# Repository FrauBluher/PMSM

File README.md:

PMSM
====

Permanent Magnet Syncronous Motor Driver and Supporting Code/Sims

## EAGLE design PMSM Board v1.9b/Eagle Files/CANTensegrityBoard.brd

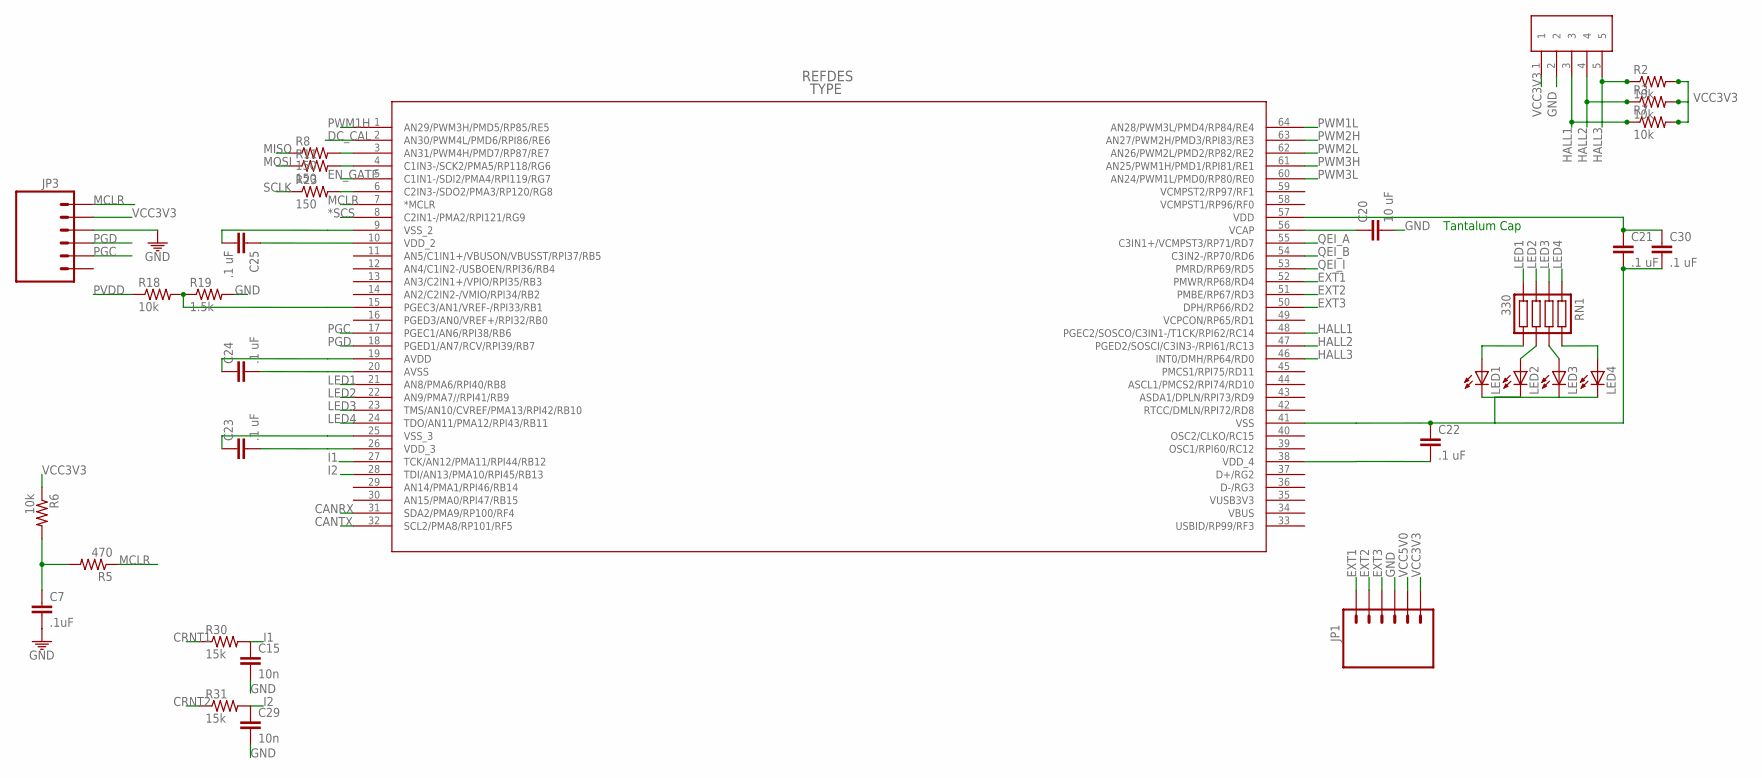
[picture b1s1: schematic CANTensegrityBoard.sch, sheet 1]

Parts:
C7: .1uF; 0805
C15, C29: 10n; 0805
C20: 10 uF; 0805
C21, C22, C23, C24, C25, C30: .1 uF; 0805
JP1: M06DUAL_ROW; 2X03
JP3: M06LOCK; 1X06_LOCK
LED1, LED2, LED3, LED4: LED0805; LED-0805
R2, R3, R6, R7, R18: 10k; 0805
R5: 470; 0805
R8, R11, R23: 150; 0805
R19: 1.5k; 0805
R30, R31: 15k; 0805
RN1: 330; EXB-38V271JV
U6: DSPIC33EP256MU80; QFP64-10X10MC
U$20: MICROCLASP5; 55932-0510

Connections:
*SCS: U6.8 (C2IN1-/PMA2/RPI121/RG9); also elsewhere on the board
CANRX: U6.31 (SDA2/PMA9/RP100/RF4); also elsewhere on the board
CANTX: U6.32 (SCL2/PMA8/RP101/RF5); also elsewhere on the board
CRNT1: R30.1; also elsewhere on the board
CRNT2: R31.1; also elsewhere on the board
DC_CAL: U6.2 (AN30/PWM4L/PMD6/RPI86/RE6); also elsewhere on the board
EN_GATE: U6.5 (C1IN1-/SDI2/PMA4/RPI119/RG7); also elsewhere on the board
EXT1: JP1.1, U6.52 (PMWR/RP68/RD4)
EXT2: JP1.2, U6.51 (PMBE/RP67/RD3)
EXT3: JP1.3, U6.50 (DPH/RP66/RD2)
GND: C7.2, C15.2, C20.2, C21.2, C22.1, C23.1, C24.2, C25.2, C29.2, C30.2, JP1.4, JP3.3, LED1.2 (C), LED2.2 (C), LED3.2 (C), LED4.2 (C), R19.2, U6.9 (VSS_2), U6.20 (AVSS), U6.25 (VSS_3), U6.41 (VSS), U$20.2; also elsewhere on the board
HALL1: R7.1, U6.48 (PGEC2/SOSCO/C3IN1-/T1CK/RPI62/RC14), U$20.3
HALL2: R3.1, U6.47 (PGED2/SOSCI/C3IN3-/RPI61/RC13), U$20.4
HALL3: R2.1, U6.46 (INT0/DMH/RP64/RD0), U$20.5
I1: C15.1, R30.2, U6.27 (TCK/AN12/PMA11/RPI44/RB12)
I2: C29.1, R31.2, U6.28 (TDI/AN13/PMA10/RPI45/RB13)
LED1: RN1.P$4 (4), U6.21 (AN8/PMA6/RPI40/RB8)
LED2: RN1.P$3 (3), U6.22 (AN9/PMA7//RPI41/RB9)
LED3: RN1.P$2 (2), U6.23 (TMS/AN10/CVREF/PMA13/RPI42/RB10)
LED4: RN1.P$1 (1), U6.24 (TDO/AN11/PMA12/RPI43/RB11)
MCLR: JP3.1, R5.1, U6.7 (*MCLR)
MISO: R8.1; also elsewhere on the board
MOSI: R11.1; also elsewhere on the board
unnamed: C7.1, R5.2, R6.2
unnamed: R8.2, U6.3 (AN31/PWM4H/PMD7/RP87/RE7)
unnamed: R11.2, U6.4 (C1IN3-/SCK2/PMA5/RP118/RG6)
unnamed: R23.2, U6.6 (C2IN3-/SDO2/PMA3/RP120/RG8)
unnamed: R18.2, R19.1, U6.15 (PGEC3/AN1/VREF-/RPI33/RB1)
unnamed: C20.1, U6.56 (VCAP)
unnamed: LED1.1 (A), RN1.P$5 (5)
unnamed: LED2.1 (A), RN1.P$6 (6)
unnamed: LED3.1 (A), RN1.P$7 (7)
unnamed: LED4.1 (A), RN1.P$8 (8)
PGC: JP3.5, U6.17 (PGEC1/AN6/RPI38/RB6)
PGD: JP3.4, U6.18 (PGED1/AN7/RCV/RPI39/RB7)
PVDD: R18.1; also elsewhere on the board
PWM1H: U6.1 (AN29/PWM3H/PMD5/RP85/RE5); also elsewhere on the board
PWM1L: U6.64 (AN28/PWM3L/PMD4/RP84/RE4); also elsewhere on the board
PWM2H: U6.63 (AN27/PWM2H/PMD3/RPI83/RE3); also elsewhere on the board
PWM2L: U6.62 (AN26/PWM2L/PMD2/RP82/RE2); also elsewhere on the board
PWM3H: U6.61 (AN25/PWM1H/PMD1/RPI81/RE1); also elsewhere on the board
PWM3L: U6.60 (AN24/PWM1L/PMD0/RP80/RE0); also elsewhere on the board
QEI_A: U6.55 (C3IN1+/VCMPST3/RP71/RD7); also elsewhere on the board
QEI_B: U6.54 (C3IN2-/RP70/RD6); also elsewhere on the board
QEI_I: U6.53 (PMRD/RP69/RD5); also elsewhere on the board
SCLK: R23.1; also elsewhere on the board
VCC3V3: C21.1, C22.2, C23.2, C24.1, C25.1, C30.1, JP1.6, JP3.2, R2.2, R3.2, R6.1, R7.2, U6.10 (VDD_2), U6.19 (AVDD), U6.26 (VDD_3), U6.38 (VDD_4), U6.57 (VDD), U$20.1; also elsewhere on the board
VCC5V0: JP1.5; also elsewhere on the board

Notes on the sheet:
Tantalum Cap

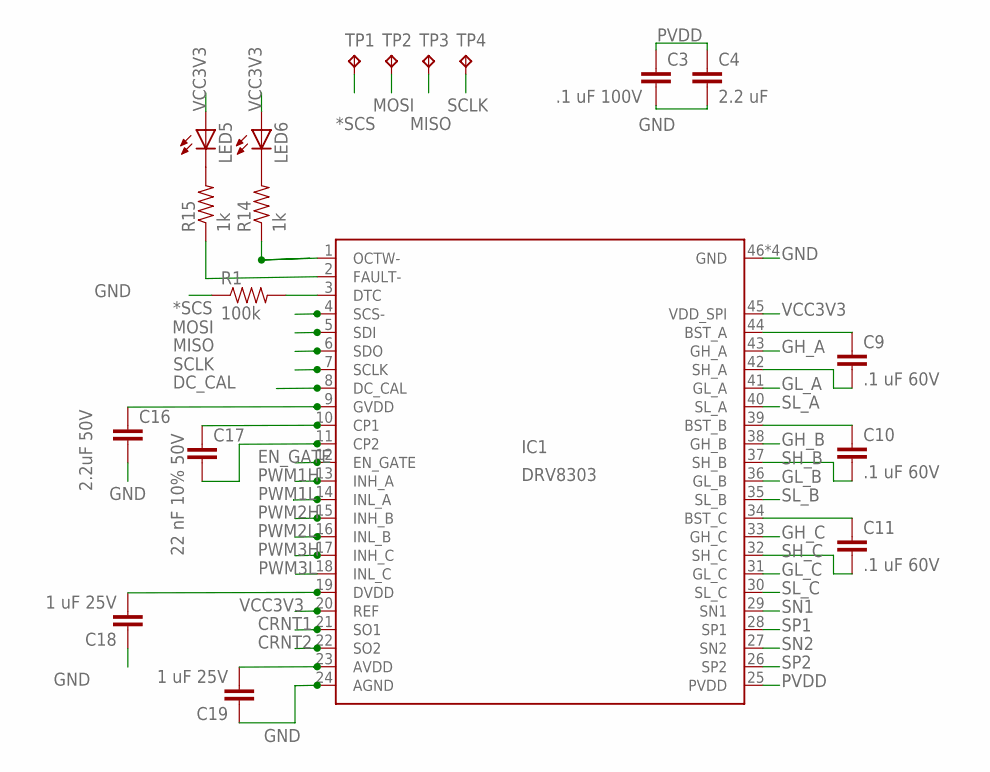
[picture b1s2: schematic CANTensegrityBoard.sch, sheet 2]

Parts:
C3: .1 uF 100V; 0805
C4: 2.2 uF; 0805
C9, C10, C11: .1 uF 60V; 0805
C16: 2.2uF 50V; 0805
C17: 22 nF 10% 50V; 0805
C18, C19: 1 uF 25V; 0805
IC1: DRV8303; HTSSOP-480-DCA
LED5, LED6: LED0805; LED-0805
R1: 100k; 0805
R14, R15: 1k; 0805
TP1, TP2, TP3, TP4: TPTP06R; TP06R

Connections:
*SCS: IC1.4 (SCS-), TP1.TP; also elsewhere on the board
BST_B: C10.1, IC1.39 (BST_B)
BST_C: C11.1, IC1.34 (BST_C)
CRNT1: IC1.21 (SO1); also elsewhere on the board
CRNT2: IC1.22 (SO2); also elsewhere on the board
DC_CAL: IC1.8 (DC_CAL); also elsewhere on the board
EN_GATE: IC1.12 (EN_GATE); also elsewhere on the board
GH_A: IC1.43 (GH_A); also elsewhere on the board
GH_B: IC1.38 (GH_B); also elsewhere on the board
GH_C: IC1.33 (GH_C); also elsewhere on the board
GL_A: IC1.41 (GL_A); also elsewhere on the board
GL_B: IC1.36 (GL_B); also elsewhere on the board
GL_C: IC1.31 (GL_C); also elsewhere on the board
GND: C3.2, C4.2, C16.2, C18.1, C19.1, IC1.24 (AGND), IC1.46 (GND), IC1.47 (GND), IC1.48 (GND), IC1.49 (GND), R1.1; also elsewhere on the board
MISO: IC1.6 (SDO), TP3.TP; also elsewhere on the board
MOSI: IC1.5 (SDI), TP2.TP; also elsewhere on the board
unnamed: IC1.3 (DTC), R1.2
unnamed: C9.1, IC1.44 (BST_A)
unnamed: LED5.2 (C), R15.2
unnamed: IC1.1 (OCTW-), R14.1
unnamed: LED6.2 (C), R14.2
unnamed: C16.1, IC1.9 (GVDD)
unnamed: C17.1, IC1.10 (CP1)
unnamed: C17.2, IC1.11 (CP2)
unnamed: C18.2, IC1.19 (DVDD)
unnamed: C19.2, IC1.23 (AVDD)
unnamed: IC1.2 (FAULT-), R15.1
PVDD: C3.1, C4.1, IC1.25 (PVDD); also elsewhere on the board
PWM1H: IC1.13 (INH_A); also elsewhere on the board
PWM1L: IC1.14 (INL_A); also elsewhere on the board
PWM2H: IC1.15 (INH_B); also elsewhere on the board
PWM2L: IC1.16 (INL_B); also elsewhere on the board
PWM3H: IC1.17 (INH_C); also elsewhere on the board
PWM3L: IC1.18 (INL_C); also elsewhere on the board
SCLK: IC1.7 (SCLK), TP4.TP; also elsewhere on the board
SH_A: C9.2, IC1.42 (SH_A); also elsewhere on the board
SH_B: C10.2, IC1.37 (SH_B); also elsewhere on the board
SH_C: C11.2, IC1.32 (SH_C); also elsewhere on the board
SL_A: IC1.40 (SL_A); also elsewhere on the board
SL_B: IC1.35 (SL_B); also elsewhere on the board
SL_C: IC1.30 (SL_C); also elsewhere on the board
SN1: IC1.29 (SN1); also elsewhere on the board
SN2: IC1.27 (SN2); also elsewhere on the board
SP1: IC1.28 (SP1); also elsewhere on the board
SP2: IC1.26 (SP2); also elsewhere on the board
VCC3V3: IC1.20 (REF), IC1.45 (VDD_SPI), LED5.1 (A), LED6.1 (A); also elsewhere on the board

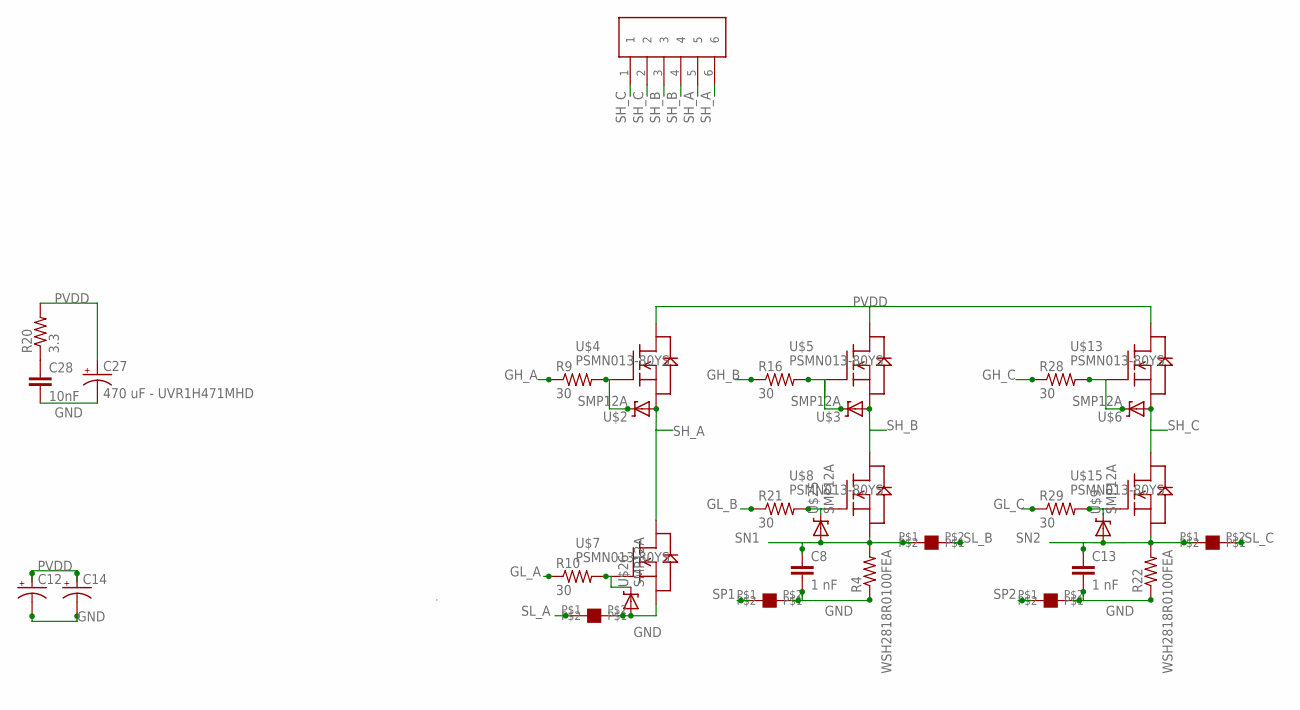
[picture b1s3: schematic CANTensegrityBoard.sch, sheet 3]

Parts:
C8, C13: 1 nF; 0805
C12, C14: CAP_POLPTH2; CPOL-RADIAL-10UF-25V
C27: 470 uF - UVR1H471MHD; CPOL-RADIAL-1000UF-25V
C28: 10nF; 0805
R4, R22: WSH2818R0100FEA; SMT-REF
R9, R10, R16, R21, R28, R29: 30; 0805
R20: 3.3; 0805
U$2, U$3, U$6, U$9, U$25, U$26: SMP12A; DO-220AA
U$4, U$5, U$7, U$8, U$13, U$15: PSMN013-80YS; TO127P600X120-5N
U$10, U$11, U$12, U$23, U$24: NETJUMPER
U$17: MINIFITJR6PIN; 0039288060

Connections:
GH_A: R9.1; also elsewhere on the board
GH_B: R16.1; also elsewhere on the board
GH_C: R28.1; also elsewhere on the board
GL_A: R10.1; also elsewhere on the board
GL_B: R21.1; also elsewhere on the board
GL_C: R29.1; also elsewhere on the board
GND: C8.2, C12.2 (-), C13.2, C14.2 (-), C27.2 (-), C28.2, R4.1, R22.1, U$7.1 (S), U$7.2 (S), U$7.3 (S), U$10.P$2, U$11.P$2, U$23.P$2, U$26.ANODE (A); also elsewhere on the board
unnamed: C28.1, R20.1
unnamed: R9.2, U$2.CATHODE (C), U$4.4 (G)
unnamed: R10.2, U$7.4 (G), U$26.CATHODE (C)
unnamed: R16.2, U$3.CATHODE (C), U$5.4 (G)
unnamed: R21.2, U$8.4 (G), U$25.CATHODE (C)
unnamed: R28.2, U$6.CATHODE (C), U$13.4 (G)
unnamed: R29.2, U$9.CATHODE (C), U$15.4 (G)
PVDD: C12.1 (+), C14.1 (+), C27.1 (+), R20.2, U$4.5 (D), U$4.P$1 (D), U$4.P$2 (D), U$4.P$3 (D), U$4.P$4 (D), U$4.P$5 (D), U$4.P$6 (D), U$4.P$7 (D), U$4.P$8 (D), U$4.P$9 (D), U$5.5 (D), U$5.P$1 (D), U$5.P$2 (D), U$5.P$3 (D), U$5.P$4 (D), U$5.P$5 (D), U$5.P$6 (D), U$5.P$7 (D), U$5.P$8 (D), U$5.P$9 (D), U$13.5 (D), U$13.P$1 (D), U$13.P$2 (D), U$13.P$3 (D), U$13.P$4 (D), U$13.P$5 (D), U$13.P$6 (D), U$13.P$7 (D), U$13.P$8 (D), U$13.P$9 (D); also elsewhere on the board
SH_A: U$2.ANODE (A), U$4.1 (S), U$4.2 (S), U$4.3 (S), U$7.5 (D), U$7.P$1 (D), U$7.P$2 (D), U$7.P$3 (D), U$7.P$4 (D), U$7.P$5 (D), U$7.P$6 (D), U$7.P$7 (D), U$7.P$8 (D), U$7.P$9 (D), U$17.5, U$17.6; also elsewhere on the board
SH_B: U$3.ANODE (A), U$5.1 (S), U$5.2 (S), U$5.3 (S), U$8.5 (D), U$8.P$1 (D), U$8.P$2 (D), U$8.P$3 (D), U$8.P$4 (D), U$8.P$5 (D), U$8.P$6 (D), U$8.P$7 (D), U$8.P$8 (D), U$8.P$9 (D), U$17.3, U$17.4; also elsewhere on the board
SH_C: U$6.ANODE (A), U$13.1 (S), U$13.2 (S), U$13.3 (S), U$15.5 (D), U$15.P$1 (D), U$15.P$2 (D), U$15.P$3 (D), U$15.P$4 (D), U$15.P$5 (D), U$15.P$6 (D), U$15.P$7 (D), U$15.P$8 (D), U$15.P$9 (D), U$17.1, U$17.2; also elsewhere on the board
SL_A: U$10.P$1; also elsewhere on the board
SL_B: U$12.P$2; also elsewhere on the board
SL_C: U$24.P$2; also elsewhere on the board
SN1: C8.1, R4.2, U$8.1 (S), U$8.2 (S), U$8.3 (S), U$12.P$1, U$25.ANODE (A); also elsewhere on the board
SN2: C13.1, R22.2, U$9.ANODE (A), U$15.1 (S), U$15.2 (S), U$15.3 (S), U$24.P$1; also elsewhere on the board
SP1: U$11.P$1; also elsewhere on the board
SP2: U$23.P$1; also elsewhere on the board

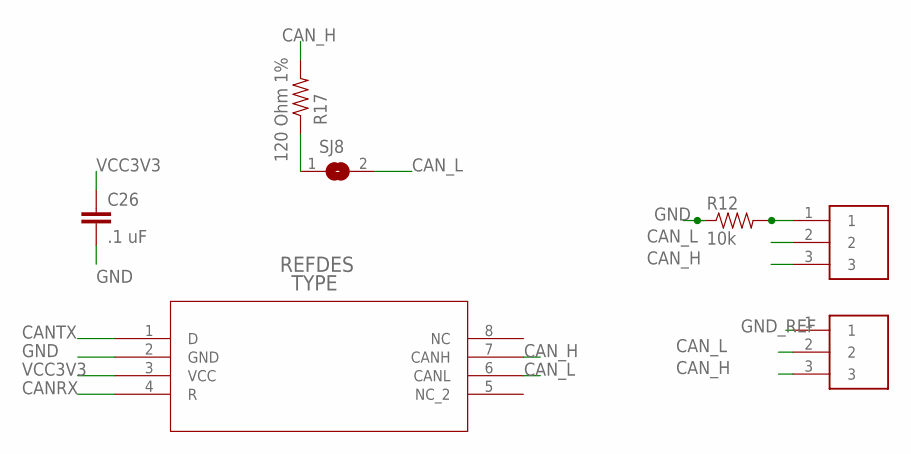
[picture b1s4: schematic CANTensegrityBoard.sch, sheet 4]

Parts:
C26: .1 uF; 0805
R12: 10k; 0805
R17: 120 Ohm 1%; 0805
SJ8: SJ
U2: SN65HVD232_D_8; D8
U$14, U$19: MICROCLASP3; 55932-0310

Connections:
CANRX: U2.4 (R); also elsewhere on the board
CANTX: U2.1 (D); also elsewhere on the board
CAN_H: R17.2, U2.7 (CANH), U$14.3, U$19.3
CAN_L: SJ8.2, U2.6 (CANL), U$14.2, U$19.2
GND: C26.2, R12.1, U2.2 (GND); also elsewhere on the board
GND_REF: R12.2, U$14.1, U$19.1
unnamed: R17.1, SJ8.1
VCC3V3: C26.1, U2.3 (VCC); also elsewhere on the board

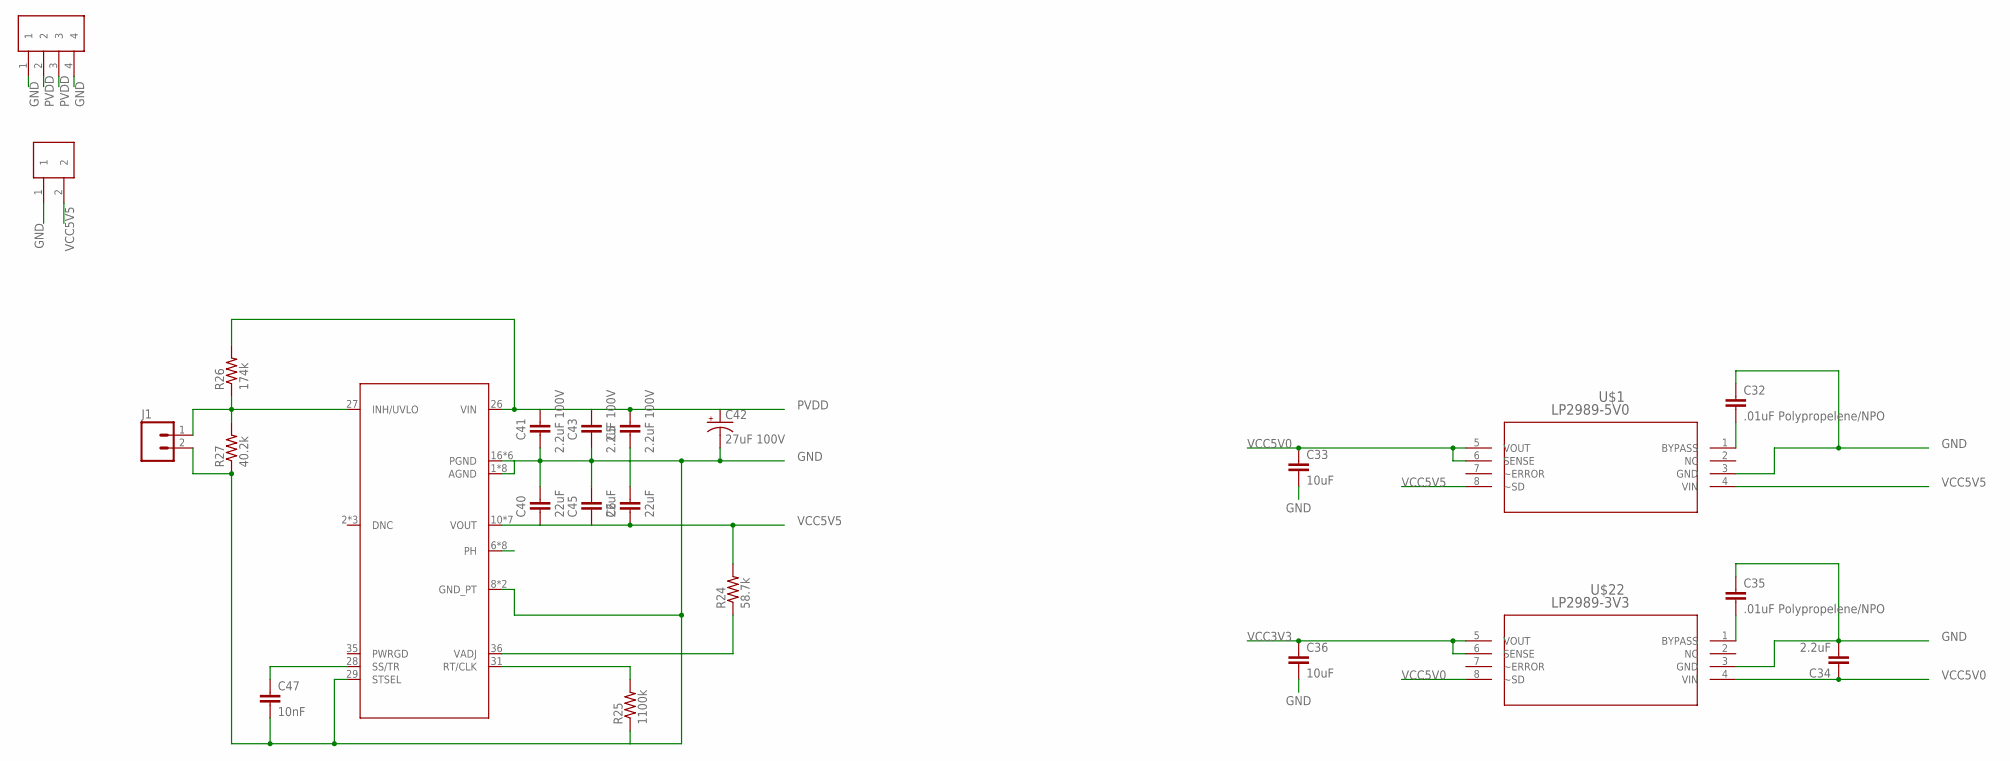
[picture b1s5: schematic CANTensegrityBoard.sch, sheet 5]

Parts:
C5, C41, C43: 2.2uF 100V; 1210
C6, C40, C45: 22uF; 1210
C32, C35: .01uF Polypropelene/NPO; 0805
C33, C36: 10uF; 0805
C34: 2.2uF; 0805
C42: 27uF 100V; CPOL-RADIAL-100UF-25V
C47: 10nF; 0805
J1: M02LOCK; 1X02_LOCK
R24: 58.7k; 0805
R25: 1100k; 0805
R26: 174k; 0805
R27: 40.2k; 0805
U7: TPS84250_RKG_41; RKG41
U$1: LP2989-5V0; MUA08A
U$16: MINIFITJR4PIN; 0039288040
U$18: MICROCLASP2; 55932-0210
U$22: LP2989-3V3; MUA08A

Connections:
GND: C5.2, C6.1, C32.1, C33.2, C34.2, C35.1, C36.2, C40.1, C41.2, C42.2 (-), C43.2, C45.1, C47.2, J1.2 (1), R25.1, R27.1, U7.1 (AGND), U7.4 (AGND), U7.5 (AGND), U7.8 (GND_PT), U7.9 (GND_PT), U7.16 (PGND), U7.17 (PGND), U7.18 (PGND), U7.19 (PGND), U7.20 (PGND), U7.29 (STSEL), U7.30 (AGND), U7.32 (AGND), U7.33 (AGND), U7.34 (AGND), U7.37 (AGND), U7.40 (PGND), U$1.3 (GND), U$16.1, U$16.4, U$18.1, U$22.3 (GND); also elsewhere on the board
unnamed: C35.2, U$22.1 (BYPASS)
unnamed: U7.6 (PH), U7.7 (PH), U7.21 (PH), U7.22 (PH), U7.23 (PH), U7.24 (PH), U7.38 (PH), U7.41 (PH)
unnamed: C32.2, U$1.1 (BYPASS)
unnamed: R24.1, U7.36 (VADJ)
unnamed: R25.2, U7.31 (RT/CLK)
unnamed: J1.1 (2), R26.1, R27.2, U7.27 (INH/UVLO)
unnamed: C47.1, U7.28 (SS/TR)
PVDD: C5.1, C41.1, C42.1 (+), C43.1, R26.2, U7.26 (VIN), U$16.2, U$16.3; also elsewhere on the board
VCC3V3: C36.1, U$22.5 (VOUT), U$22.6 (SENSE); also elsewhere on the board
VCC5V0: C33.1, C34.1, U$1.5 (VOUT), U$1.6 (SENSE), U$22.4 (VIN), U$22.8 (~SD); also elsewhere on the board
VCC5V5: C6.2, C40.2, C45.2, R24.2, U7.10 (VOUT), U7.11 (VOUT), U7.12 (VOUT), U7.13 (VOUT), U7.14 (VOUT), U7.15 (VOUT), U7.39 (VOUT), U$1.4 (VIN), U$1.8 (~SD), U$18.2

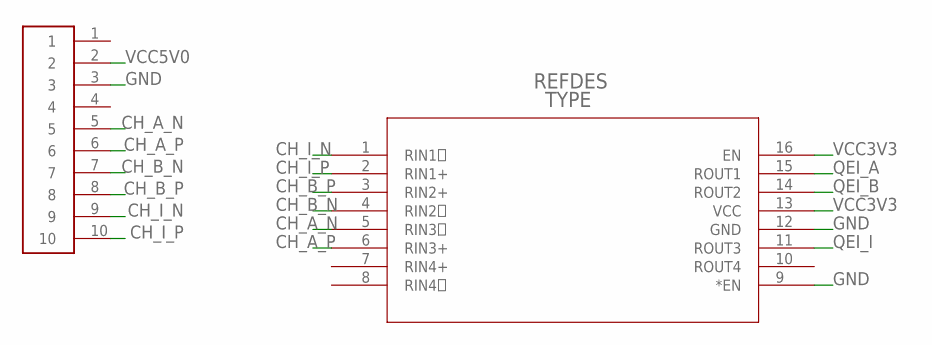
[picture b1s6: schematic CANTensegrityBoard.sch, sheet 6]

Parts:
U3: SN65LVDT348_PW_1; PW16
U$21: 3M10PIN2500; FOUR-WALL-2500-LP-STH

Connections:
CH_A_N: U3.5 (RIN3), U$21.5
CH_A_P: U3.6 (RIN3+), U$21.6
CH_B_N: U3.4 (RIN2), U$21.7
CH_B_P: U3.3 (RIN2+), U$21.8
CH_I_N: U3.1 (RIN1), U$21.9
CH_I_P: U3.2 (RIN1+), U$21.10
GND: U3.9 (*EN), U3.12 (GND), U$21.3; also elsewhere on the board
QEI_A: U3.15 (ROUT1); also elsewhere on the board
QEI_B: U3.14 (ROUT2); also elsewhere on the board
QEI_I: U3.11 (ROUT3); also elsewhere on the board
VCC3V3: U3.13 (VCC), U3.16 (EN); also elsewhere on the board
VCC5V0: U$21.2; also elsewhere on the board

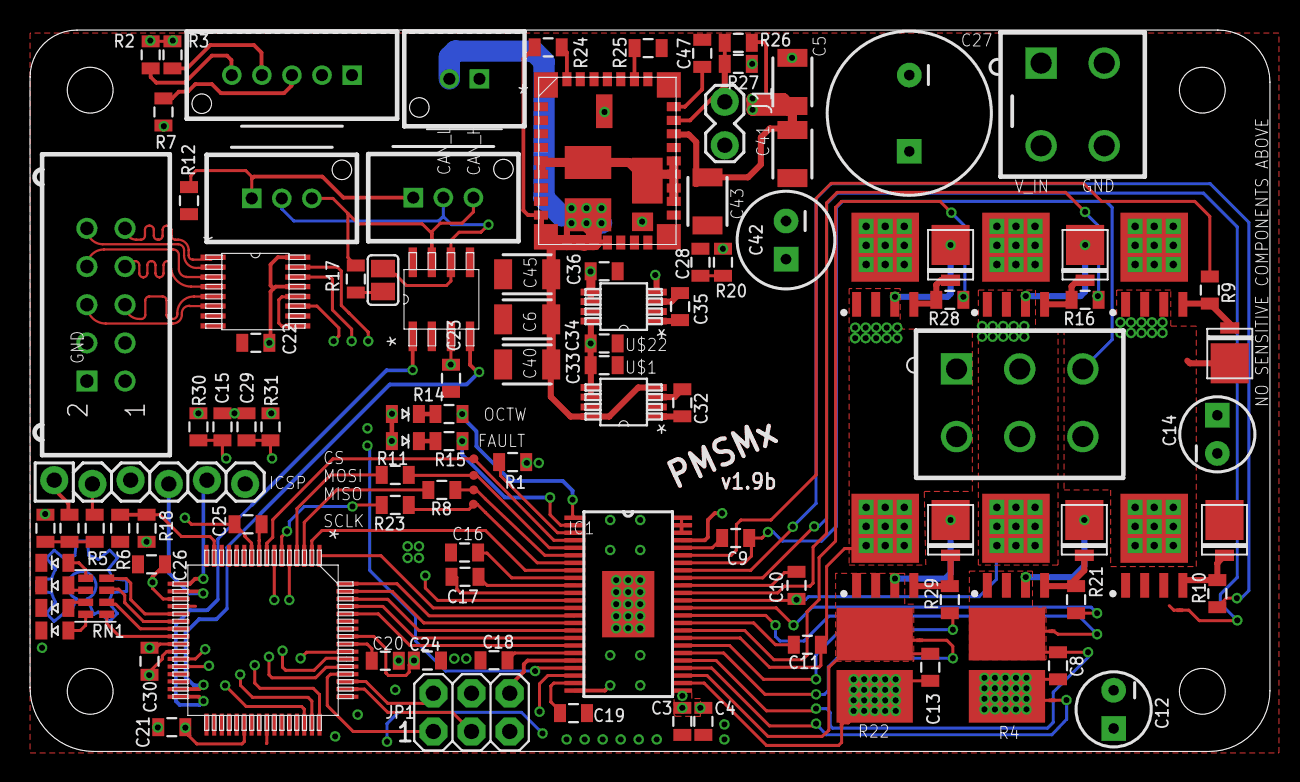
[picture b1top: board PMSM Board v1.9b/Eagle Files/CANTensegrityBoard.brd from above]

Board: 4 copper layers, 82.5 x 48.0 mm, 119 parts (0 on the bottom side), 102 nets.

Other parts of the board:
E$1, E$2, E$3, E$4: STAND-OFF-TIGHT

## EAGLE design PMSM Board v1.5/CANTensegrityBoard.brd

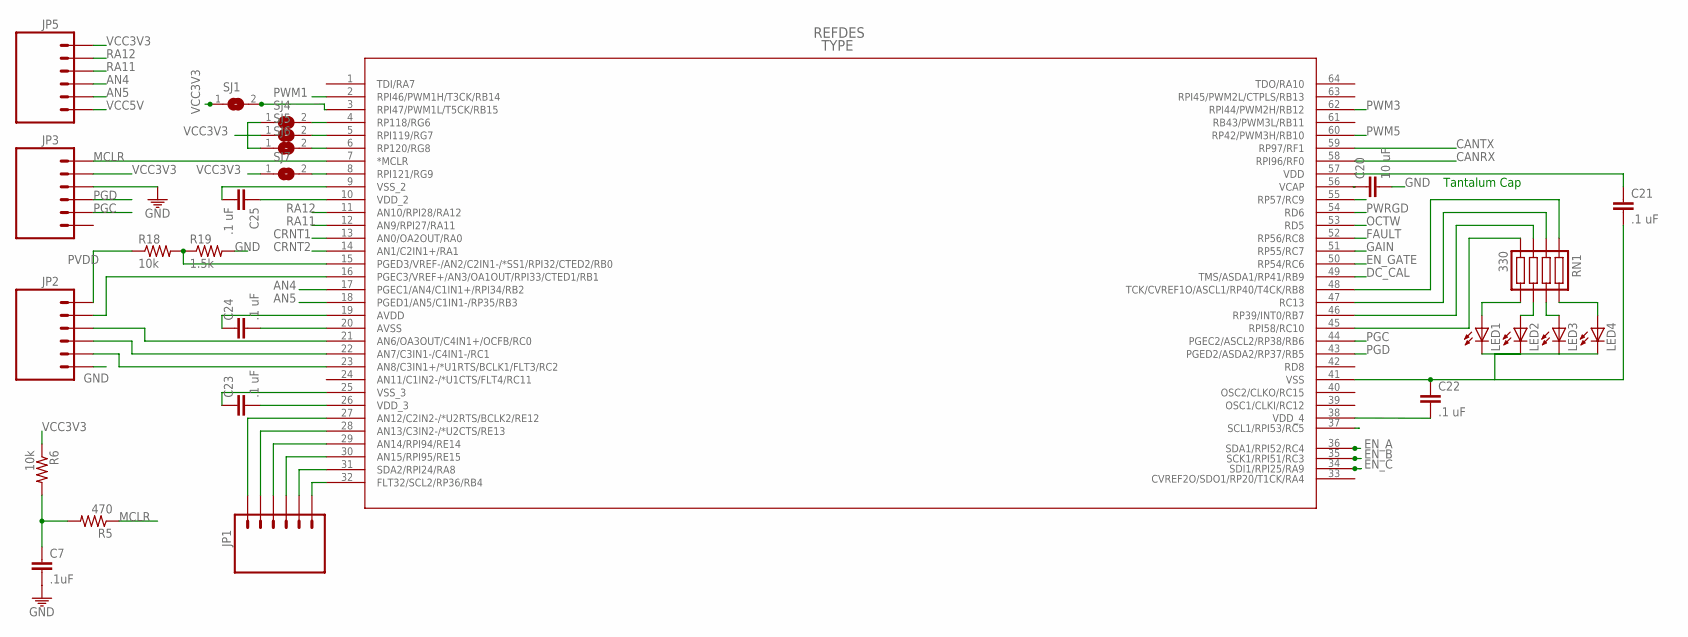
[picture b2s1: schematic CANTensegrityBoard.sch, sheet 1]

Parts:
C7: .1uF; 0805
C20: 10 uF; 1206
C21, C22, C23, C24, C25: .1 uF; 0805
JP1, JP2: M06SIP; 1X06
JP3, JP5: M06LOCK; 1X06_LOCK
LED1, LED2, LED3, LED4: LED0805; LED-0805
R5: 470; 0805
R6, R18: 10k; 0805
R19: 1.5k; 0805
RN1: 330; EXB-38V271JV
SJ1, SJ4, SJ5, SJ6, SJ7: SJ
U$1: DSPIC33EP128MC502-I/SS; QFP64-10X10MC

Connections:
AN4: JP5.4, U$1.17 (PGEC1/AN4/C1IN1+/RPI34/RB2)
AN5: JP5.5, U$1.18 (PGED1/AN5/C1IN1-/RP35/RB3)
CANRX: U$1.58 (RPI96/RF0); also elsewhere on the board
CANTX: U$1.59 (RP97/RF1); also elsewhere on the board
CRNT1: U$1.13 (AN0/OA2OUT/RA0); also elsewhere on the board
CRNT2: U$1.14 (AN1/C2IN1+/RA1); also elsewhere on the board
DC_CAL: U$1.49 (TMS/ASDA1/RP41/RB9); also elsewhere on the board
EN_A: U$1.36 (SDA1/RPI52/RC4); also elsewhere on the board
EN_B: U$1.35 (SCK1/RPI51/RC3); also elsewhere on the board
EN_C: U$1.34 (SDI1/RPI25/RA9); also elsewhere on the board
EN_GATE: U$1.50 (RP54/RC6); also elsewhere on the board
FAULT: U$1.52 (RP56/RC8); also elsewhere on the board
GAIN: U$1.51 (RP55/RC7); also elsewhere on the board
GND: C7.2, C20.2, C21.2, C22.1, C23.1, C24.2, C25.2, JP2.6, JP3.3, LED1.2 (C), LED2.2 (C), LED3.2 (C), LED4.2 (C), R19.2, U$1.9 (VSS_2), U$1.20 (AVSS), U$1.25 (VSS_3), U$1.41 (VSS); also elsewhere on the board
MCLR: JP3.1, R5.1, U$1.7 (*MCLR)
unnamed: C7.1, R5.2, R6.2
unnamed: SJ1.2, U$1.3 (RPI47/PWM1L/T5CK/RB15)
unnamed: R18.2, R19.1, U$1.15 (PGED3/VREF-/AN2/C2IN1-/*SS1/RPI32/CTED2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)
unnamed: SJ4.2, U$1.4 (RP118/RG6)
unnamed: SJ5.2, U$1.5 (RPI119/RG7)
unnamed: SJ6.2, U$1.6 (RP120/RG8)
unnamed: SJ7.2, U$1.8 (RPI121/RG9)
unnamed: C20.1, U$1.56 (VCAP)
unnamed: RN1.P$1 (1), U$1.48 (TCK/CVREF1O/ASCL1/RP40/T4CK/RB8)
unnamed: RN1.P$2 (2), U$1.47 (RC13)
unnamed: RN1.P$3 (3), U$1.46 (RP39/INT0/RB7)
unnamed: RN1.P$4 (4), U$1.45 (RPI58/RC10)
unnamed: LED1.1 (A), RN1.P$5 (5)
unnamed: LED2.1 (A), RN1.P$6 (6)
unnamed: LED3.1 (A), RN1.P$7 (7)
unnamed: LED4.1 (A), RN1.P$8 (8)
unnamed: JP1.6, U$1.32 (FLT32/SCL2/RP36/RB4)
unnamed: JP1.5, U$1.31 (SDA2/RPI24/RA8)
unnamed: JP1.4, U$1.30 (AN15/RPI95/RE15)
unnamed: JP1.3, U$1.29 (AN14/RPI94/RE14)
unnamed: JP1.2, U$1.28 (AN13/C3IN2-/*U2CTS/RE13)
unnamed: JP1.1, U$1.27 (AN12/C2IN2-/*U2RTS/BCLK2/RE12)
unnamed: JP2.2, U$1.16 (PGEC3/VREF+/AN3/OA1OUT/RPI33/CTED1/RB1)
unnamed: JP2.3, U$1.21 (AN6/OA3OUT/C4IN1+/OCFB/RC0)
unnamed: JP2.4, U$1.22 (AN7/C3IN1-/C4IN1-/RC1)
unnamed: JP2.5, U$1.23 (AN8/C3IN1+/*U1RTS/BCLK1/FLT3/RC2)
OCTW: U$1.53 (RD5); also elsewhere on the board
PGC: JP3.5, U$1.44 (PGEC2/ASCL2/RP38/RB6)
PGD: JP3.4, U$1.43 (PGED2/ASDA2/RP37/RB5)
PVDD: JP2.1, R18.1; also elsewhere on the board
PWM1: U$1.2 (RPI46/PWM1H/T3CK/RB14); also elsewhere on the board
PWM3: U$1.62 (RPI44/PWM2H/RB12); also elsewhere on the board
PWM5: U$1.60 (RP42/PWM3H/RB10); also elsewhere on the board
PWRGD: U$1.54 (RD6); also elsewhere on the board
RA11: JP5.3, U$1.12 (AN9/RPI27/RA11)
RA12: JP5.2, U$1.11 (AN10/RPI28/RA12)
RC9: U$1.55 (RP57/RC9)
VCC3V3: C21.1, C22.2, C23.2, C24.1, C25.1, JP3.2, JP5.1, R6.1, SJ1.1, SJ4.1, SJ5.1, SJ6.1, SJ7.1, U$1.10 (VDD_2), U$1.19 (AVDD), U$1.26 (VDD_3), U$1.38 (VDD_4), U$1.57 (VDD); also elsewhere on the board
VCC5V: JP5.6; also elsewhere on the board

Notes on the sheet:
Tantalum Cap

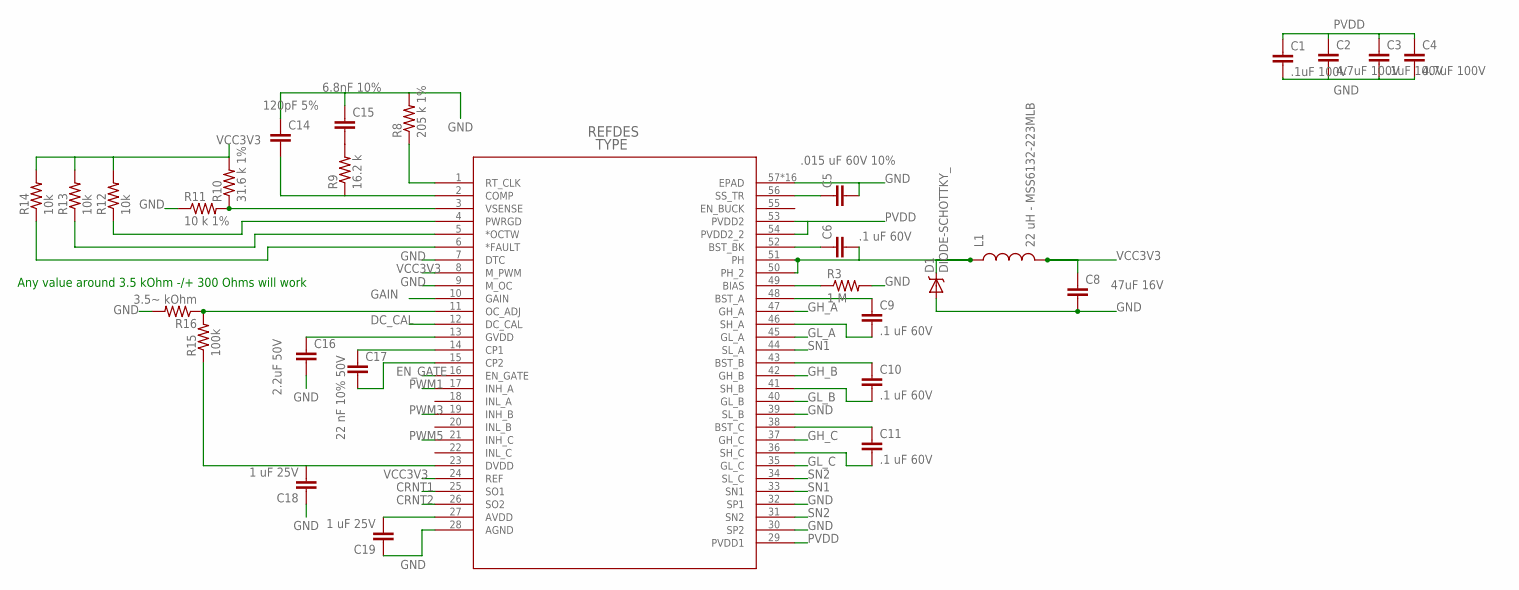
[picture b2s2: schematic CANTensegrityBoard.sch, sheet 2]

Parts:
C1, C3: .1uF 100V; 0805
C2, C4: 4.7uF 100V; 1206
C5: .015 uF 60V 10%; 0805
C6, C9, C10, C11: .1 uF 60V; 0805
C8: 47uF 16V; 1206
C14: 120pF 5%; 0805
C15: 6.8nF 10%; 0805
C16: 2.2uF 50V; 1206
C17: 22 nF 10% 50V; 0805
C18, C19: 1 uF 25V; 0805
D1: DIODE-SCHOTTKY_; SMA-DIODE
L1: 22 uH - MSS6132-223MLB; MSS6132
R3: 1 M; 0805
R8: 205 k 1%; 0805
R9: 16.2 k; 0805
R10: 31.6 k 1%; 0805
R11: 10 k 1%; 0805
R12, R13, R14: 10k; 0805
R15: 100k; 0805
R16: 3.5~ kOhm; 0805
U$2: DRV8302; DCA56_6P35X3P600

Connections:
CRNT1: U$2.25 (SO1); also elsewhere on the board
CRNT2: U$2.26 (SO2); also elsewhere on the board
DC_CAL: U$2.12 (DC_CAL); also elsewhere on the board
EN_GATE: U$2.16 (EN_GATE); also elsewhere on the board
FAULT: R14.1, U$2.6 (*FAULT); also elsewhere on the board
GAIN: U$2.10 (GAIN); also elsewhere on the board
GH_A: U$2.47 (GH_A); also elsewhere on the board
GH_B: U$2.42 (GH_B); also elsewhere on the board
GH_C: U$2.37 (GH_C); also elsewhere on the board
GL_A: U$2.45 (GL_A); also elsewhere on the board
GL_B: U$2.40 (GL_B); also elsewhere on the board
GL_C: U$2.35 (GL_C); also elsewhere on the board
GND: C1.2, C2.2, C3.2, C4.2, C5.2, C8.2, C14.1, C15.1, C16.2, C18.1, C19.1, D1.A, R3.2, R8.2, R11.1, R16.2, U$2.7 (DTC), U$2.9 (M_OC), U$2.28 (AGND), U$2.30 (SP2), U$2.32 (SP1), U$2.39 (SL_B), U$2.57 (EPAD), U$2.P$1 (EPAD), U$2.P$2 (EPAD), U$2.P$3 (EPAD), U$2.P$4 (EPAD), U$2.P$5 (EPAD), U$2.P$6 (EPAD), U$2.P$7 (EPAD), U$2.P$8 (EPAD), U$2.P$9 (EPAD), U$2.P$10 (EPAD), U$2.P$11 (EPAD), U$2.P$12 (EPAD), U$2.P$13 (EPAD), U$2.P$14 (EPAD), U$2.P$15 (EPAD); also elsewhere on the board
unnamed: C5.1, U$2.56 (SS_TR)
unnamed: C6.1, U$2.52 (BST_BK)
unnamed: R3.1, U$2.49 (BIAS)
unnamed: C9.1, U$2.48 (BST_A)
unnamed: C10.1, U$2.43 (BST_B)
unnamed: C11.1, U$2.38 (BST_C)
unnamed: R8.1, U$2.1 (RT_CLK)
unnamed: C15.2, R9.2
unnamed: C14.2, R9.1, U$2.2 (COMP)
unnamed: R10.1, R11.2, U$2.3 (VSENSE)
unnamed: C16.1, U$2.13 (GVDD)
unnamed: C17.1, U$2.14 (CP1)
unnamed: C17.2, U$2.15 (CP2)
unnamed: C18.2, R15.1, U$2.23 (DVDD)
unnamed: C19.2, U$2.27 (AVDD)
unnamed: R15.2, R16.1, U$2.11 (OC_ADJ)
OCTW: R13.1, U$2.5 (*OCTW); also elsewhere on the board
OUT_U: C9.2, U$2.46 (SH_A); also elsewhere on the board
OUT_V: C10.2, U$2.41 (SH_B); also elsewhere on the board
OUT_W: C11.2, U$2.36 (SH_C); also elsewhere on the board
PH1: C6.2, D1.C, L1.P$1 (1), U$2.51 (PH)
PVDD: C1.1, C2.1, C3.1, C4.1, U$2.29 (PVDD1), U$2.53 (PVDD2), U$2.54 (PVDD2_2); also elsewhere on the board
PWM1: U$2.17 (INH_A); also elsewhere on the board
PWM3: U$2.19 (INH_B); also elsewhere on the board
PWM5: U$2.21 (INH_C); also elsewhere on the board
PWRGD: R12.1, U$2.4 (PWRGD); also elsewhere on the board
SN1: U$2.33 (SN1), U$2.44 (SL_A); also elsewhere on the board
SN2: U$2.31 (SN2), U$2.34 (SL_C); also elsewhere on the board
VCC3V3: C8.1, L1.P$2 (2), R10.2, R12.2, R13.2, R14.2, U$2.8 (M_PWM), U$2.24 (REF); also elsewhere on the board

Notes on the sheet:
Any value around 3.5 kOhm -/+ 300 Ohms will work

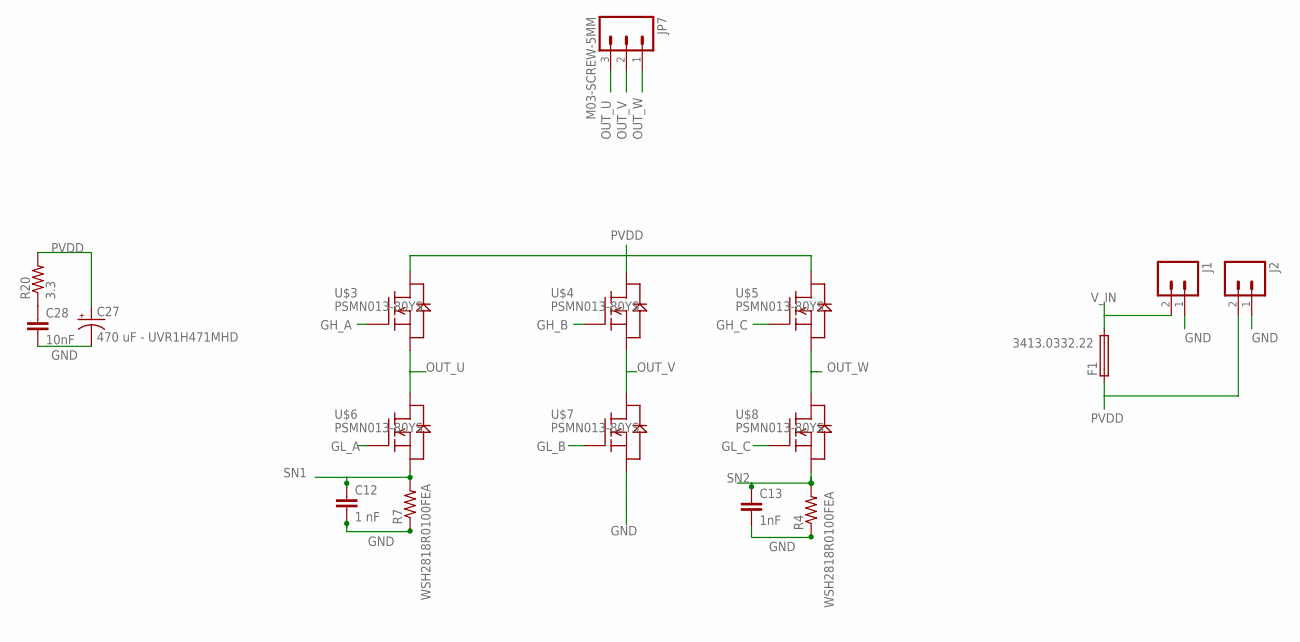
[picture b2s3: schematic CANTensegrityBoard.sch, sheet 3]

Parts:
C12: 1 nF; 0805
C13: 1nF; 0805
C27: 470 uF - UVR1H471MHD; CPOL-RADIAL-1000UF-25V
C28: 10nF; 0805
F1: 3413.0332.22; LED-1206
J1, J2: M02PTH4; 1X02_XTRA_BIG
JP7: M03-SCREW-5MM; SCREWTERMINAL-5MM-3
R4, R7: WSH2818R0100FEA; SMT-REF
R20: 3.3; 0805
U$3, U$4, U$5, U$6, U$7, U$8: PSMN013-80YS; TO127P600X120-5N

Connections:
GH_A: U$3.4 (G); also elsewhere on the board
GH_B: U$4.4 (G); also elsewhere on the board
GH_C: U$5.4 (G); also elsewhere on the board
GL_A: U$6.4 (G); also elsewhere on the board
GL_B: U$7.4 (G); also elsewhere on the board
GL_C: U$8.4 (G); also elsewhere on the board
GND: C12.2, C13.2, C27.2 (-), C28.2, J1.1 (2), J2.1 (2), R4.1, R7.1, U$7.1 (S), U$7.2 (S), U$7.3 (S); also elsewhere on the board
unnamed: C28.1, R20.1
OUT_U: JP7.3, U$3.1 (S), U$3.2 (S), U$3.3 (S), U$6.5 (D), U$6.P$1 (D), U$6.P$2 (D), U$6.P$3 (D), U$6.P$4 (D), U$6.P$5 (D), U$6.P$6 (D), U$6.P$7 (D), U$6.P$8 (D), U$6.P$9 (D); also elsewhere on the board
OUT_V: JP7.2, U$4.1 (S), U$4.2 (S), U$4.3 (S), U$7.5 (D), U$7.P$1 (D), U$7.P$2 (D), U$7.P$3 (D), U$7.P$4 (D), U$7.P$5 (D), U$7.P$6 (D), U$7.P$7 (D), U$7.P$8 (D), U$7.P$9 (D); also elsewhere on the board
OUT_W: JP7.1, U$5.1 (S), U$5.2 (S), U$5.3 (S), U$8.5 (D), U$8.P$1 (D), U$8.P$2 (D), U$8.P$3 (D), U$8.P$4 (D), U$8.P$5 (D), U$8.P$6 (D), U$8.P$7 (D), U$8.P$8 (D), U$8.P$9 (D); also elsewhere on the board
PVDD: C27.1 (+), F1.A (1), J2.2 (1), R20.2, U$3.5 (D), U$3.P$1 (D), U$3.P$2 (D), U$3.P$3 (D), U$3.P$4 (D), U$3.P$5 (D), U$3.P$6 (D), U$3.P$7 (D), U$3.P$8 (D), U$3.P$9 (D), U$4.5 (D), U$4.P$1 (D), U$4.P$2 (D), U$4.P$3 (D), U$4.P$4 (D), U$4.P$5 (D), U$4.P$6 (D), U$4.P$7 (D), U$4.P$8 (D), U$4.P$9 (D), U$5.5 (D), U$5.P$1 (D), U$5.P$2 (D), U$5.P$3 (D), U$5.P$4 (D), U$5.P$5 (D), U$5.P$6 (D), U$5.P$7 (D), U$5.P$8 (D), U$5.P$9 (D); also elsewhere on the board
SN1: C12.1, R7.2, U$6.1 (S), U$6.2 (S), U$6.3 (S); also elsewhere on the board
SN2: C13.1, R4.2, U$8.1 (S), U$8.2 (S), U$8.3 (S); also elsewhere on the board
V_IN: F1.C (2), J1.2 (1)

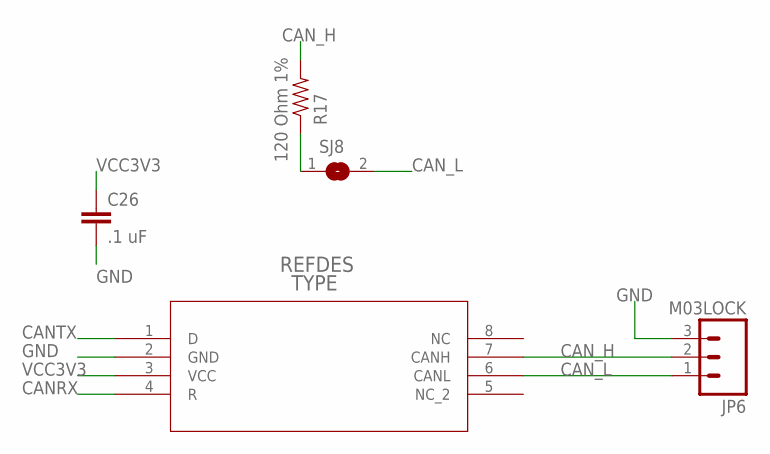
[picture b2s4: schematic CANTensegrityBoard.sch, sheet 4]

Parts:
C26: .1 uF; 0805
JP6: M03LOCK; 1X03_LOCK
R17: 120 Ohm 1%; 0805
SJ8: SJ
U2: SN65HVD232_D_8; D8

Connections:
CANRX: U2.4 (R); also elsewhere on the board
CANTX: U2.1 (D); also elsewhere on the board
CAN_H: JP6.2, R17.2, U2.7 (CANH)
CAN_L: JP6.1, SJ8.2, U2.6 (CANL)
GND: C26.2, JP6.3, U2.2 (GND); also elsewhere on the board
unnamed: R17.1, SJ8.1
VCC3V3: C26.1, U2.3 (VCC); also elsewhere on the board

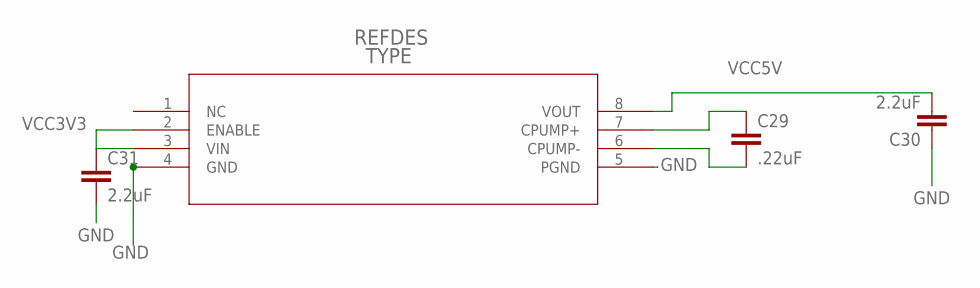
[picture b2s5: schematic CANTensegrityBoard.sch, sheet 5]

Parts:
C29: .22uF; 0805
C30, C31: 2.2uF; 0805
U1: REG711-5_DGK_8; DGK8

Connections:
GND: C30.1, C31.2, U1.4 (GND), U1.5 (PGND); also elsewhere on the board
unnamed: C29.2, U1.6 (CPUMP-)
unnamed: C29.1, U1.7 (CPUMP+)
VCC3V3: C31.1, U1.2 (ENABLE), U1.3 (VIN); also elsewhere on the board
VCC5V: C30.2, U1.8 (VOUT); also elsewhere on the board

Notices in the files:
PMSM Board v1.5/CANTensegrityBoard.brd:
Licensed under the TAPR OHL
